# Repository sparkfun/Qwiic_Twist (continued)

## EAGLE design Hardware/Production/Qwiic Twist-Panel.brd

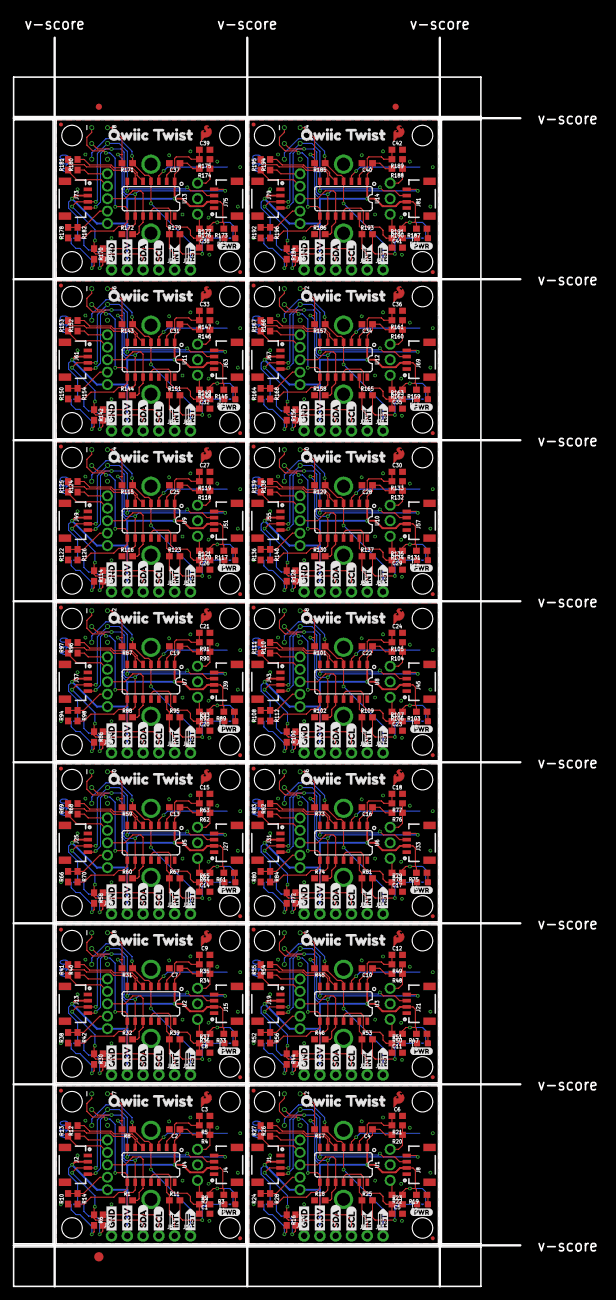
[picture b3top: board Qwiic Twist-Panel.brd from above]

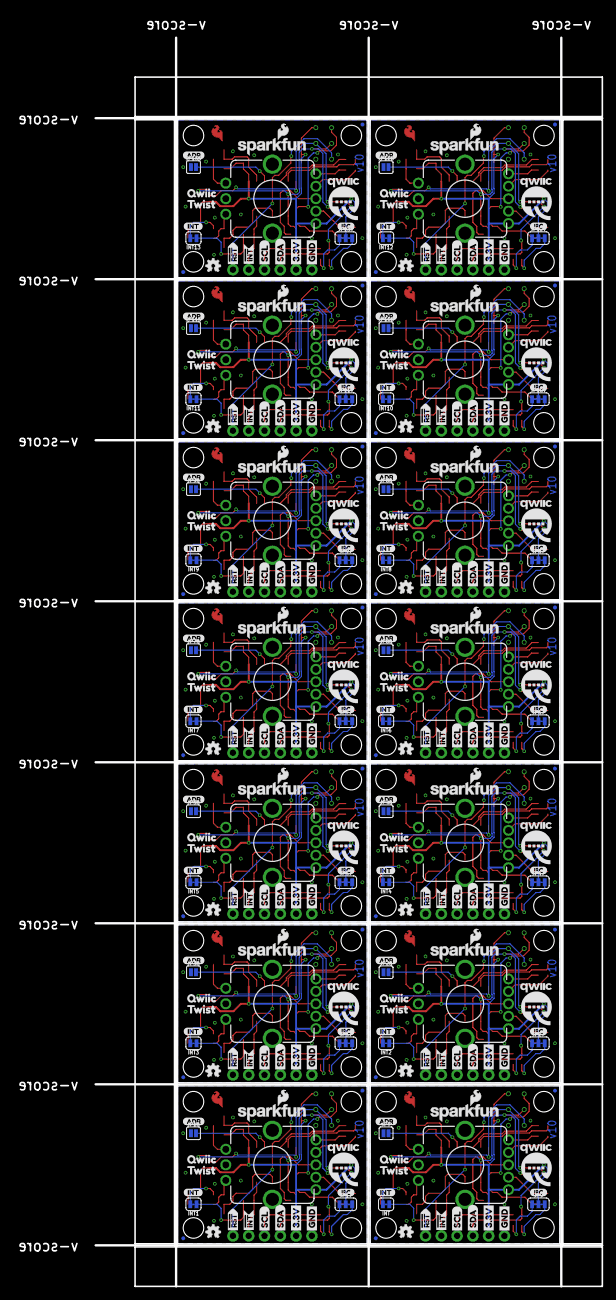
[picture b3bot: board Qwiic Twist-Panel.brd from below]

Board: 2 copper layers, 94.7 x 204.8 mm, 843 parts (280 on the bottom side), 308 nets.

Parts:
C1, C3, C5, C6, C8, C9, C11, C12, C14, C15, C17, C18, C20, C21, C23, C24, C26, C27, C29, C30, C32, C33, C35, C36, C38, C39, C41, C42: 10nF; 0603
C2, C4, C7, C10, C13, C16, C19, C22, C25, C28, C31, C34, C37, C40: 0.1uF; 0603
D1, D2, D3, D4, D5, D6, D7, D8, D9, D10, D11, D12, D13, D14: RED; LED-0603
E$1, E$2: FIDUCIAL-1X2
E$3: FIDUCIAL-1.5X3
INT, INT1, INT2, INT3, INT4, INT5, INT6, INT7, INT8, INT9, INT10, INT11, INT12, INT13: SMT-JUMPER_2_NC_TRACE_SILK
J1, J2, J4, J8, J13, J15, J19, J21, J25, J27, J31, J33, J37, J39, J43, J45, J49, J51, J55, J57, J61, J63, J67, J69, J73, J75, J79, J81: 1X04_1MM_RA
J3, J6, J14, J20, J26, J32, J38, J44, J50, J56, J62, J68, J74, J80: PTH; 1X04_NO_SILK
J5, J9, J10, J11, J16, J17, J22, J23, J28, J29, J34, J35, J40, J41, J46, J47, J52, J53, J58, J59, J64, J65, J70, J71, J76, J77, J82, J83: 1X01_NO_SILK
J7, J12, J18, J24, J30, J36, J42, J48, J54, J60, J66, J72, J78, J84: ISP; 2X3_TEST_POINTS
JP1, JP2, JP5, JP6, JP12, JP14, JP15, JP20, JP23, JP24, JP25, JP30, JP33, JP34, JP35, JP40, JP43, JP44, JP45, JP50, JP53, JP54, JP55, JP60, JP63, JP64, JP65, JP70, JP73, JP74, JP75, JP80, JP83, JP84, JP85, JP90, JP93, JP94, JP95, JP100, JP103, JP104, JP105, JP110, JP113, JP114, JP115, JP120, JP123, JP124, JP125, JP130, JP133, JP134, JP135, JP140: FIDUCIALUFIDUCIAL; MICRO-FIDUCIAL
JP3, JP4, JP8, JP10, JP11, JP13, JP18, JP19, JP21, JP22, JP28, JP29, JP31, JP32, JP38, JP39, JP41, JP42, JP48, JP49, JP51, JP52, JP58, JP59, JP61, JP62, JP68, JP69, JP71, JP72, JP78, JP79, JP81, JP82, JP88, JP89, JP91, JP92, JP98, JP99, JP101, JP102, JP108, JP109, JP111, JP112, JP118, JP119, JP121, JP122, JP128, JP129, JP131, JP132, JP138, JP139: STAND-OFF
JP7, JP16, JP26, JP36, JP46, JP56, JP66, JP76, JP86, JP96, JP106, JP116, JP126, JP136: ADR; SMT-JUMPER_2_NO_SILK
JP9, JP17, JP27, JP37, JP47, JP57, JP67, JP77, JP87, JP97, JP107, JP117, JP127, JP137: SMT-JUMPER_3_2-NC_TRACE_SILK
LOGO1, LOGO4, LOGO7, LOGO10, LOGO13, LOGO16, LOGO19, LOGO22, LOGO25, LOGO28, LOGO31, LOGO34, LOGO37, LOGO40: OSHW-LOGOMINI; OSHW-LOGO-MINI
LOGO2, LOGO5, LOGO8, LOGO11, LOGO14, LOGO17, LOGO20, LOGO23, LOGO26, LOGO29, LOGO32, LOGO35, LOGO38, LOGO41: SFE_LOGO_NAME_FLAME.1_INCH; SFE_LOGO_NAME_FLAME_.1
LOGO3, LOGO6, LOGO9, LOGO12, LOGO15, LOGO18, LOGO21, LOGO24, LOGO27, LOGO30, LOGO33, LOGO36, LOGO39, LOGO42: SFE_LOGO_FLAME.1EXP; SFE_LOGO_FLAME_COPPER_EXPOSED_.1
R1, R4, R5, R7, R8, R9, R11, R17, R18, R20, R21, R22, R23, R25, R31, R32, R34, R35, R36, R37, R39, R45, R46, R48, R49, R50, R51, R53, R59, R60, R62, R63, R64, R65, R67, R73, R74, R76, R77, R78, R79, R81, R87, R88, R90, R91, R92, R93, R95, R101, R102, R104, R105, R106, R107, R109, R115, R116, R118, R119, R120, R121, R123, R129, R130, R132, R133, R134, R135, R137, R143, R144, R146, R147, R148, R149, R151, R157, R158, R160, R161, R162, R163, R165, R171, R172, R174, R175, R176, R177, R179, R185, R186, R188, R189, R190, R191, R193: 10k; 0603
R2, R6, R15, R16, R29, R30, R43, R44, R57, R58, R71, R72, R85, R86, R99, R100, R113, R114, R127, R128, R141, R142, R155, R156, R169, R170, R183, R184: 2.2k; 0603
R3, R19, R33, R47, R61, R75, R89, R103, R117, R131, R145, R159, R173, R187: 1k; 0603
R10, R24, R38, R52, R66, R80, R94, R108, R122, R136, R150, R164, R178, R192: DNP; 0603
R12, R13, R14, R26, R27, R28, R40, R41, R42, R54, R55, R56, R68, R69, R70, R82, R83, R84, R96, R97, R98, R110, R111, R112, R124, R125, R126, R138, R139, R140, R152, R153, R154, R166, R167, R168, R180, R181, R182, R194, R195, R196: 10; 0603
SW1, SW2, SW3, SW4, SW5, SW6, SW7, SW8, SW9, SW10, SW11, SW12, SW13, SW14: Rotary Encoder; ENCODER_LED_3_KIT
U1, U2, U3, U4, U5, U6, U7, U8, U9, U10, U11, U12, U13, U14: ATTINY84-ARDUINO; SO14
U$1, U$36, U$57, U$77, U$97, U$117, U$137, U$157, U$177, U$197, U$217, U$237, U$257, U$277: QWIIC1
U$2, U$39, U$60, U$80, U$100, U$120, U$140, U$160, U$180, U$200, U$220, U$240, U$260, U$280: INT0
U$3, U$13, U$20, U$22, U$41, U$44, U$62, U$65, U$82, U$85, U$102, U$105, U$122, U$125, U$142, U$145, U$162, U$165, U$182, U$185, U$202, U$205, U$222, U$225, U$242, U$245, U$262, U$265: GND1
U$4, U$10, U$21, U$23, U$40, U$45, U$61, U$66, U$81, U$86, U$101, U$106, U$121, U$126, U$141, U$146, U$161, U$166, U$181, U$186, U$201, U$206, U$221, U$226, U$241, U$246, U$261, U$266: 3#3V2
U$5, U$19, U$24, U$27, U$43, U$46, U$64, U$67, U$84, U$87, U$104, U$107, U$124, U$127, U$144, U$147, U$164, U$167, U$184, U$187, U$204, U$207, U$224, U$227, U$244, U$247, U$264, U$267: SDA8
U$6, U$15, U$25, U$26, U$42, U$48, U$63, U$68, U$83, U$88, U$103, U$108, U$123, U$128, U$143, U$148, U$163, U$168, U$183, U$188, U$203, U$208, U$223, U$228, U$243, U$248, U$263, U$268: SCL9
U$7, U$16, U$31, U$32, U$52, U$53, U$72, U$73, U$92, U$93, U$112, U$113, U$132, U$133, U$152, U$153, U$172, U$173, U$192, U$193, U$212, U$213, U$232, U$233, U$252, U$253, U$272, U$273: RST#-[>
U$8, U$28, U$49, U$69, U$89, U$109, U$129, U$149, U$169, U$189, U$209, U$229, U$249, U$269: I_SUPER2_C-()-03
U$9, U$11, U$29, U$30, U$50, U$51, U$70, U$71, U$90, U$91, U$110, U$111, U$130, U$131, U$150, U$151, U$170, U$171, U$190, U$191, U$210, U$211, U$230, U$231, U$250, U$251, U$270, U$271: INT#-[<
U$12, U$37, U$58, U$78, U$98, U$118, U$138, U$158, U$178, U$198, U$218, U$238, U$258, U$278: TWIST2
U$14, U$38, U$59, U$79, U$99, U$119, U$139, U$159, U$179, U$199, U$219, U$239, U$259, U$279: QWIIC_TWIST1
U$17, U$33, U$54, U$74, U$94, U$114, U$134, U$154, U$174, U$194, U$214, U$234, U$254, U$274: PWR-()-03
U$18, U$34, U$55, U$75, U$95, U$115, U$135, U$155, U$175, U$195, U$215, U$235, U$255, U$275: ADR-()-03
U$35, U$47, U$56, U$76, U$96, U$116, U$136, U$156, U$176, U$196, U$216, U$236, U$256, U$276: QWIIC-LOGO-MEDIUM

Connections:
3.3V: C2.1, INT.2, J2.2, J3.2, J4.2, J7.2, JP9.2, R3.2, R4.2, R7.1, R8.2, SW1.5, U4.1
3.3V1: C4.1, INT1.2, J1.2, J6.2, J8.2, J12.2, JP17.2, R17.2, R19.2, R20.2, R22.1, SW2.5, U1.1
3.3V2: C7.1, INT2.2, J13.2, J14.2, J15.2, J18.2, JP27.2, R31.2, R33.2, R34.2, R36.1, SW3.5, U2.1
3.3V3: C10.1, INT3.2, J19.2, J20.2, J21.2, J24.2, JP37.2, R45.2, R47.2, R48.2, R50.1, SW4.5, U3.1
3.3V4: C13.1, INT4.2, J25.2, J26.2, J27.2, J30.2, JP47.2, R59.2, R61.2, R62.2, R64.1, SW5.5, U5.1
3.3V5: C16.1, INT5.2, J31.2, J32.2, J33.2, J36.2, JP57.2, R73.2, R75.2, R76.2, R78.1, SW6.5, U6.1
3.3V6: C19.1, INT6.2, J37.2, J38.2, J39.2, J42.2, JP67.2, R87.2, R89.2, R90.2, R92.1, SW7.5, U7.1
3.3V7: C22.1, INT7.2, J43.2, J44.2, J45.2, J48.2, JP77.2, R101.2, R103.2, R104.2, R106.1, SW8.5, U8.1
3.3V8: C25.1, INT8.2, J49.2, J50.2, J51.2, J54.2, JP87.2, R115.2, R117.2, R118.2, R120.1, SW9.5, U9.1
3.3V9: C28.1, INT9.2, J55.2, J56.2, J57.2, J60.2, JP97.2, R129.2, R131.2, R132.2, R134.1, SW10.5, U10.1
3.3V10: C31.1, INT10.2, J61.2, J62.2, J63.2, J66.2, JP107.2, R143.2, R145.2, R146.2, R148.1, SW11.5, U11.1
3.3V11: C34.1, INT11.2, J67.2, J68.2, J69.2, J72.2, JP117.2, R157.2, R159.2, R160.2, R162.1, SW12.5, U12.1
3.3V12: C37.1, INT12.2, J73.2, J74.2, J75.2, J78.2, JP127.2, R171.2, R173.2, R174.2, R176.1, SW13.5, U13.1
3.3V13: C40.1, INT13.2, J79.2, J80.2, J81.2, J84.2, JP137.2, R185.2, R187.2, R188.2, R190.1, SW14.5, U14.1
!INT: J5.1, R11.1, U4.13
!INT1: J9.1, R25.1, U1.13
!INT2: J16.1, R39.1, U2.13
!INT3: J22.1, R53.1, U3.13
!INT4: J28.1, R67.1, U5.13
!INT5: J34.1, R81.1, U6.13
!INT6: J40.1, R95.1, U7.13
!INT7: J46.1, R109.1, U8.13
!INT8: J52.1, R123.1, U9.13
!INT9: J58.1, R137.1, U10.13
!INT10: J64.1, R151.1, U11.13
!INT11: J70.1, R165.1, U12.13
!INT12: J76.1, R179.1, U13.13
!INT13: J82.1, R193.1, U14.13
!RST: J7.5, J10.1, R8.1, U4.4
!RST1: J11.1, J12.5, R17.1, U1.4
!RST2: J17.1, J18.5, R31.1, U2.4
!RST3: J23.1, J24.5, R45.1, U3.4
!RST4: J29.1, J30.5, R59.1, U5.4
!RST5: J35.1, J36.5, R73.1, U6.4
!RST6: J41.1, J42.5, R87.1, U7.4
!RST7: J47.1, J48.5, R101.1, U8.4
!RST8: J53.1, J54.5, R115.1, U9.4
!RST9: J59.1, J60.5, R129.1, U10.4
!RST10: J65.1, J66.5, R143.1, U11.4
!RST11: J71.1, J72.5, R157.1, U12.4
!RST12: J77.1, J78.5, R171.1, U13.4
!RST13: J83.1, J84.5, R185.1, U14.4
A: R4.1, R5.1, SW1.A
A1: R20.1, R21.1, SW2.A
A2: R34.1, R35.1, SW3.A
A3: R48.1, R49.1, SW4.A
A4: R62.1, R63.1, SW5.A
A5: R76.1, R77.1, SW6.A
A6: R90.1, R91.1, SW7.A
A7: R104.1, R105.1, SW8.A
A8: R118.1, R119.1, SW9.A
A9: R132.1, R133.1, SW10.A
A10: R146.1, R147.1, SW11.A
A11: R160.1, R161.1, SW12.A
A12: R174.1, R175.1, SW13.A
A13: R188.1, R189.1, SW14.A
ADR: JP7.2, U4.3
ADR1: JP16.2, U1.3
ADR2: JP26.2, U2.3
ADR3: JP36.2, U3.3
ADR4: JP46.2, U5.3
ADR5: JP56.2, U6.3
ADR6: JP66.2, U7.3
ADR7: JP76.2, U8.3
ADR8: JP86.2, U9.3
ADR9: JP96.2, U10.3
ADR10: JP106.2, U11.3
ADR11: JP116.2, U12.3
ADR12: JP126.2, U13.3
ADR13: JP136.2, U14.3
B: R7.2, R9.2, SW1.B
B1: R22.2, R23.2, SW2.B
B2: R36.2, R37.2, SW3.B
B3: R50.2, R51.2, SW4.B
B4: R64.2, R65.2, SW5.B
B5: R78.2, R79.2, SW6.B
B6: R92.2, R93.2, SW7.B
B7: R106.2, R107.2, SW8.B
B8: R120.2, R121.2, SW9.B
B9: R134.2, R135.2, SW10.B
B10: R148.2, R149.2, SW11.B
B11: R162.2, R163.2, SW12.B
B12: R176.2, R177.2, SW13.B
B13: R190.2, R191.2, SW14.B
BLUE: J7.1, R14.2, U4.8
BLUE1: J12.1, R28.2, U1.8
BLUE2: J18.1, R42.2, U2.8
BLUE3: J24.1, R56.2, U3.8
BLUE4: J30.1, R70.2, U5.8
BLUE5: J36.1, R84.2, U6.8
BLUE6: J42.1, R98.2, U7.8
BLUE7: J48.1, R112.2, U8.8
BLUE8: J54.1, R126.2, U9.8
BLUE9: J60.1, R140.2, U10.8
BLUE10: J66.1, R154.2, U11.8
BLUE11: J72.1, R168.2, U12.8
BLUE12: J78.1, R182.2, U13.8
BLUE13: J84.1, R196.2, U14.8
BLUE_RAW: R10.2, R14.1, SW1.4
BLUE_RAW1: R24.2, R28.1, SW2.4
BLUE_RAW2: R38.2, R42.1, SW3.4
BLUE_RAW3: R52.2, R56.1, SW4.4
BLUE_RAW4: R66.2, R70.1, SW5.4
BLUE_RAW5: R80.2, R84.1, SW6.4
BLUE_RAW6: R94.2, R98.1, SW7.4
BLUE_RAW7: R108.2, R112.1, SW8.4
BLUE_RAW8: R122.2, R126.1, SW9.4
BLUE_RAW9: R136.2, R140.1, SW10.4
BLUE_RAW10: R150.2, R154.1, SW11.4
BLUE_RAW11: R164.2, R168.1, SW12.4
BLUE_RAW12: R178.2, R182.1, SW13.4
BLUE_RAW13: R192.2, R196.1, SW14.4
ENCODER_A: C3.1, R5.2, U4.2
ENCODER_A1: C6.1, R21.2, U1.2
ENCODER_A2: C9.1, R35.2, U2.2
ENCODER_A3: C12.1, R49.2, U3.2
ENCODER_A4: C15.1, R63.2, U5.2
ENCODER_A5: C18.1, R77.2, U6.2
ENCODER_A6: C21.1, R91.2, U7.2
ENCODER_A7: C24.1, R105.2, U8.2
ENCODER_A8: C27.1, R119.2, U9.2
ENCODER_A9: C30.1, R133.2, U10.2
ENCODER_A10: C33.1, R147.2, U11.2
ENCODER_A11: C36.1, R161.2, U12.2
ENCODER_A12: C39.1, R175.2, U13.2
ENCODER_A13: C42.1, R189.2, U14.2
ENCODER_B: C1.1, R9.1, U4.11
ENCODER_B1: C5.1, R23.1, U1.11
ENCODER_B2: C8.1, R37.1, U2.11
ENCODER_B3: C11.1, R51.1, U3.11
ENCODER_B4: C14.1, R65.1, U5.11
ENCODER_B5: C17.1, R79.1, U6.11
ENCODER_B6: C20.1, R93.1, U7.11
ENCODER_B7: C23.1, R107.1, U8.11
ENCODER_B8: C26.1, R121.1, U9.11
ENCODER_B9: C29.1, R135.1, U10.11
ENCODER_B10: C32.1, R149.1, U11.11
ENCODER_B11: C35.1, R163.1, U12.11
ENCODER_B12: C38.1, R177.1, U13.11
ENCODER_B13: C41.1, R191.1, U14.11
GND: C1.2, C2.2, C3.2, D1.C, J2.1, J3.1, J4.1, J7.6, JP7.1, R1.1, R10.1, SW1.C, U4.14
GND1: C4.2, C5.2, C6.2, D2.C, J1.1, J6.1, J8.1, J12.6, JP16.1, R18.1, R24.1, SW2.C, U1.14
GND2: C7.2, C8.2, C9.2, D3.C, J13.1, J14.1, J15.1, J18.6, JP26.1, R32.1, R38.1, SW3.C, U2.14
GND3: C10.2, C11.2, C12.2, D4.C, J19.1, J20.1, J21.1, J24.6, JP36.1, R46.1, R52.1, SW4.C, U3.14
GND4: C13.2, C14.2, C15.2, D5.C, J25.1, J26.1, J27.1, J30.6, JP46.1, R60.1, R66.1, SW5.C, U5.14
GND5: C16.2, C17.2, C18.2, D6.C, J31.1, J32.1, J33.1, J36.6, JP56.1, R74.1, R80.1, SW6.C, U6.14
GND6: C19.2, C20.2, C21.2, D7.C, J37.1, J38.1, J39.1, J42.6, JP66.1, R88.1, R94.1, SW7.C, U7.14
GND7: C22.2, C23.2, C24.2, D8.C, J43.1, J44.1, J45.1, J48.6, JP76.1, R102.1, R108.1, SW8.C, U8.14
GND8: C25.2, C26.2, C27.2, D9.C, J49.1, J50.1, J51.1, J54.6, JP86.1, R116.1, R122.1, SW9.C, U9.14
GND9: C28.2, C29.2, C30.2, D10.C, J55.1, J56.1, J57.1, J60.6, JP96.1, R130.1, R136.1, SW10.C, U10.14
GND10: C31.2, C32.2, C33.2, D11.C, J61.1, J62.1, J63.1, J66.6, JP106.1, R144.1, R150.1, SW11.C, U11.14
GND11: C34.2, C35.2, C36.2, D12.C, J67.1, J68.1, J69.1, J72.6, JP116.1, R158.1, R164.1, SW12.C, U12.14
GND12: C37.2, C38.2, C39.2, D13.C, J73.1, J74.1, J75.1, J78.6, JP126.1, R172.1, R178.1, SW13.C, U13.14
GND13: C40.2, C41.2, C42.2, D14.C, J79.1, J80.1, J81.1, J84.6, JP136.1, R186.1, R192.1, SW14.C, U14.14
GREEN: R13.2, U4.6
GREEN1: R27.2, U1.6
GREEN2: R41.2, U2.6
GREEN3: R55.2, U3.6
GREEN4: R69.2, U5.6
GREEN5: R83.2, U6.6
GREEN6: R97.2, U7.6
GREEN7: R111.2, U8.6
GREEN8: R125.2, U9.6
GREEN9: R139.2, U10.6
GREEN10: R153.2, U11.6
GREEN11: R167.2, U12.6
GREEN12: R181.2, U13.6
GREEN13: R195.2, U14.6
GREEN_RAW: R13.1, SW1.2
GREEN_RAW1: R27.1, SW2.2
GREEN_RAW2: R41.1, SW3.2
GREEN_RAW3: R55.1, SW4.2
GREEN_RAW4: R69.1, SW5.2
GREEN_RAW5: R83.1, SW6.2
GREEN_RAW6: R97.1, SW7.2
GREEN_RAW7: R111.1, SW8.2
GREEN_RAW8: R125.1, SW9.2
GREEN_RAW9: R139.1, SW10.2
GREEN_RAW10: R153.1, SW11.2
GREEN_RAW11: R167.1, SW12.2
GREEN_RAW12: R181.1, SW13.2
GREEN_RAW13: R195.1, SW14.2
INT_R: INT.1, R11.2
INT_R1: INT1.1, R25.2
INT_R2: INT2.1, R39.2
INT_R3: INT3.1, R53.2
INT_R4: INT4.1, R67.2
INT_R5: INT5.1, R81.2
INT_R6: INT6.1, R95.2
INT_R7: INT7.1, R109.2
INT_R8: INT8.1, R123.2
INT_R9: INT9.1, R137.2
INT_R10: INT10.1, R151.2
INT_R11: INT11.1, R165.2
INT_R12: INT12.1, R179.2
INT_R13: INT13.1, R193.2
unnamed: D2.A, R19.1
unnamed: D3.A, R33.1
unnamed: D1.A, R3.1
unnamed: D4.A, R47.1
unnamed: D5.A, R61.1
unnamed: D6.A, R75.1
unnamed: D7.A, R89.1
unnamed: D8.A, R103.1
unnamed: D9.A, R117.1
unnamed: D10.A, R131.1
unnamed: D11.A, R145.1
unnamed: D12.A, R159.1
unnamed: D13.A, R173.1
unnamed: D14.A, R187.1
RED: R12.2, U4.5
RED1: R26.2, U1.5
RED2: R40.2, U2.5
RED3: R54.2, U3.5
RED4: R68.2, U5.5
RED5: R82.2, U6.5
RED6: R96.2, U7.5
RED7: R110.2, U8.5
RED8: R124.2, U9.5
RED9: R138.2, U10.5
RED10: R152.2, U11.5
RED11: R166.2, U12.5
RED12: R180.2, U13.5
RED13: R194.2, U14.5
RED_RAW: R12.1, SW1.1
RED_RAW1: R26.1, SW2.1
RED_RAW2: R40.1, SW3.1
RED_RAW3: R54.1, SW4.1
RED_RAW4: R68.1, SW5.1
RED_RAW5: R82.1, SW6.1
RED_RAW6: R96.1, SW7.1
RED_RAW7: R110.1, SW8.1
RED_RAW8: R124.1, SW9.1
RED_RAW9: R138.1, SW10.1
RED_RAW10: R152.1, SW11.1
RED_RAW11: R166.1, SW12.1
RED_RAW12: R180.1, SW13.1
RED_RAW13: R194.1, SW14.1
SCL: J2.4, J3.4, J4.4, J7.3, R2.1, U4.9
SCL1: J1.4, J6.4, J8.4, J12.3, R15.1, U1.9
SCL2: J13.4, J14.4, J15.4, J18.3, R29.1, U2.9
SCL3: J19.4, J20.4, J21.4, J24.3, R43.1, U3.9
SCL4: J25.4, J26.4, J27.4, J30.3, R57.1, U5.9
SCL5: J31.4, J32.4, J33.4, J36.3, R71.1, U6.9
SCL6: J37.4, J38.4, J39.4, J42.3, R85.1, U7.9
SCL7: J43.4, J44.4, J45.4, J48.3, R99.1, U8.9
SCL8: J49.4, J50.4, J51.4, J54.3, R113.1, U9.9
SCL9: J55.4, J56.4, J57.4, J60.3, R127.1, U10.9
SCL10: J61.4, J62.4, J63.4, J66.3, R141.1, U11.9
SCL11: J67.4, J68.4, J69.4, J72.3, R155.1, U12.9
SCL12: J73.4, J74.4, J75.4, J78.3, R169.1, U13.9
SCL13: J79.4, J80.4, J81.4, J84.3, R183.1, U14.9
SCL_PU1: JP9.1, R2.2
SCL_PU2: JP17.1, R15.2
SCL_PU3: JP27.1, R29.2
SCL_PU4: JP37.1, R43.2
SCL_PU5: JP47.1, R57.2
SCL_PU6: JP57.1, R71.2
SCL_PU7: JP67.1, R85.2
SCL_PU8: JP77.1, R99.2
SCL_PU9: JP87.1, R113.2
SCL_PU10: JP97.1, R127.2
SCL_PU11: JP107.1, R141.2
SCL_PU12: JP117.1, R155.2
SCL_PU13: JP127.1, R169.2
SCL_PU14: JP137.1, R183.2
SDA: J2.3, J3.3, J4.3, J7.4, R6.1, U4.7
SDA1: J1.3, J6.3, J8.3, J12.4, R16.1, U1.7
SDA2: J13.3, J14.3, J15.3, J18.4, R30.1, U2.7
SDA3: J19.3, J20.3, J21.3, J24.4, R44.1, U3.7
SDA4: J25.3, J26.3, J27.3, J30.4, R58.1, U5.7
SDA5: J31.3, J32.3, J33.3, J36.4, R72.1, U6.7
SDA6: J37.3, J38.3, J39.3, J42.4, R86.1, U7.7
SDA7: J43.3, J44.3, J45.3, J48.4, R100.1, U8.7
SDA8: J49.3, J50.3, J51.3, J54.4, R114.1, U9.7
SDA9: J55.3, J56.3, J57.3, J60.4, R128.1, U10.7
SDA10: J61.3, J62.3, J63.3, J66.4, R142.1, U11.7
SDA11: J67.3, J68.3, J69.3, J72.4, R156.1, U12.7
SDA12: J73.3, J74.3, J75.3, J78.4, R170.1, U13.7
SDA13: J79.3, J80.3, J81.3, J84.4, R184.1, U14.7
SDA_PU1: JP9.3, R6.2
SDA_PU2: JP17.3, R16.2
SDA_PU3: JP27.3, R30.2
SDA_PU4: JP37.3, R44.2
SDA_PU5: JP47.3, R58.2
SDA_PU6: JP57.3, R72.2
SDA_PU7: JP67.3, R86.2
SDA_PU8: JP77.3, R100.2
SDA_PU9: JP87.3, R114.2
SDA_PU10: JP97.3, R128.2
SDA_PU11: JP107.3, R142.2
SDA_PU12: JP117.3, R156.2
SDA_PU13: JP127.3, R170.2
SDA_PU14: JP137.3, R184.2
SWITCH: R1.2, SW1.3, U4.10
SWITCH1: R18.2, SW2.3, U1.10
SWITCH2: R32.2, SW3.3, U2.10
SWITCH3: R46.2, SW4.3, U3.10
SWITCH4: R60.2, SW5.3, U5.10
SWITCH5: R74.2, SW6.3, U6.10
SWITCH6: R88.2, SW7.3, U7.10
SWITCH7: R102.2, SW8.3, U8.10
SWITCH8: R116.2, SW9.3, U9.10
SWITCH9: R130.2, SW10.3, U10.10
SWITCH10: R144.2, SW11.3, U11.10
SWITCH11: R158.2, SW12.3, U12.10
SWITCH12: R172.2, SW13.3, U13.10
SWITCH13: R186.2, SW14.3, U14.10

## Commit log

2018-11-13 Increasing panel size for better production.
2018-11-15 Adding test sketch showing how to reference byte inside a struct
2018-12-03 Main firmware works with memory map. Auto-clearing of certain variables does not work.
2018-12-03 Production firmware working.
2018-12-03 Timestamps working
2018-12-04 Add I2C address error checking.
2018-12-04 Removing old test files
2018-12-04 Removing old files
2019-01-24 Changing interrupt control to a state machine
    This reduces the amount of int pin toggling as seen in this issue: https://forum.sparkfun.com/viewtopic.php?f=14&t=49095
2019-04-28 Adding dimensions to board
2019-05-20 Adding ignore. Fix I2C addresses in schematic. Add dims and new sch pdfs.
2019-05-27 First Step: Clean up all compiler warnings. Briefly tested this new version, and no behavior changes were observed.
2019-05-27 Added new feature: New register called Rotation Limit. If set to non-zero value, it will force EncoderCount to 'wrap around' at Rotation Limit, and also prevent EncoderCount from going below zero. Te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
2019-07-11 Update License Section
    remove TS email... add forum link
2021-08-27 Add programming instructions
2021-08-27 Update programming readme. Add mark indicator.
